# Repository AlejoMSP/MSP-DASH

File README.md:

# MSP-DASH

A digital gauge cluster for a turbocharged 2002 Mazda Miata (NB2) running rusEFI. Three round AMOLED screens show
gauges; one ESP32 "hub" reads the car (CAN bus and its own sensors) and sends everything to them over ESP-NOW.
A small OLED on the hub shows warning lamps and quick pages.

Power in the car (fuse, diode, TVS, buck options): docs/POWER.md.

The stock tach and speedo: `aircore/` (ESP32 DevKitC + two DRV8833 at 5 V, aircore build 8; set up on the hub's Stock gauges page). Pinout and calibration: aircore/README.md.

Current builds: **screens 245**, **hub 70**.

## Hardware

| Board | Role | Address |
|---|---|---|
| ESP32 DevKitC (Freenove terminal board) | **Hub**: CAN, sensors, buttons, brightness, OLED, GPS, accelerometer, 433 MHz | 192.168.55.204 |
| Waveshare ESP32-S3-Touch-AMOLED-1.43 (466x466) | **Left** screen | 192.168.55.201 |
| same | **Center** screen (also logs to its SD card) | 192.168.55.202 |
| same | **Right** screen | 192.168.55.203 |

Hub peripherals: SN65HVD230 CAN transceiver, MAX6675 (EGT), DHT22 (cabin temp/humidity), fuel level sender, GT-U7 GPS,
CC1101 433 MHz receiver (TPMS, in progress), 0.96" SSD1306 OLED, MPU6050 accelerometer, optional MCP23017 input
expanders, optional ADS1115 analog expanders, two page buttons, dash dimmer and lights-on inputs. Every GPIO with its terminal:
[docs/HUB_PINS.md](docs/HUB_PINS.md) (kept in step with `esp32-input/hub_pins.h` by a test).

## What it does

**Screens** (`esp32s3-amoled-bsp-base/`, LVGL 8 on Waveshare's BSP)
- Up to 8 named pages, each a 1-cell, 2-up, 3-up or 2x2 layout of needle, number, half-moon or trend-graph gauges, or
  a page of indicator lamps.
- Per gauge: signal, range, ticks, warning (flash or full-screen alert), peak hold, caption and value placement by
  coordinates, needle thickness and glow, 79 car icons (Material Design Icons) beside or instead of the caption.
- 10 contrast-checked colour schemes, switchable live from a button.
- Web editor with a live screen preview of each cell (caption, icon, sample value, colours), web dashboard,
  OTA updates.
- SD logging on the center screen: start conditions (key on, RPM, speed, any sensor), log files named by the GPS
  date and time, a time column, button log markers.
- Clock gauge from the GPS time (12/24 hour).

**Hub** (`esp32-input/`)
- rusEFI over CAN (DBC-matched), ECU detection, 16 configurable custom CAN sensors (`/custom`).
- Own sensors: EGT, cabin temp/humidity, fuel level, GPS speed/time, accelerometer (lateral, accel/brake and vertical
  G, yaw rate), lamp inputs.
- Brightness from the car's lights and dimmer (or a knob), with day/night levels.
- Inputs and pins page: every GPIO and expander pin with what uses it; move any function to another GPIO; up to 16 inputs on free pins as buttons (active LOW or HIGH, press and hold actions), switches or analog sensors (pressure, voltage, temperature presets, or custom) feeding custom sensor slots; up to 16 outputs (relays, LEDs) switched by a signal, an input or a button.
- Two buttons, configurable on `/buttons`: press or hold 1/2/3/5/10 s, left/right/both. Actions: next/previous page,
  choose screen, go to page, dim/brighten, colour scheme, race mode, clear warning, log marker, show IPs, OLED next page.
- OLED warning panel (`/oled`): 8 lamps with icons, WARNING and DANGER levels, signal or wire-input triggers, plus
  pages (big number, values, G-meter, clock); a lit lamp takes the screen over.
- Bench simulator (`/simulator`) that drives every screen without the car.
- One web app at the hub's address, with a side menu: Dashboard (status tiles, warning panel, key readings), Setup (brightness, clock, accelerometer, I2C devices), Screens (each screen's own pages, picked Left / Center / Right), OLED, Live and custom sensors, Buttons, Logging, Firmware, Simulator, Raw CAN, 433 MHz.

## Getting started

New PC setup (arduino-cli, ESP32 core 3.3.11, libraries, `lv_conf.h`): [PREREQUISITES.md](PREREQUISITES.md).
Copy `esp32-input/wifi_config.h.example` to `wifi_config.h` (and the same for the screens) with your WiFi details.

### Flashing (PowerShell)

Hub (it builds with a few shared headers from the screen folder, copied in first):

```powershell
cls
cd C:\Users\alejo\OneDrive\GIT\MSP-DASH
git pull origin main
copy C:\Users\alejo\OneDrive\GIT\MSP-DASH\esp32s3-amoled-bsp-base\can_parsing.h,C:\Users\alejo\OneDrive\GIT\MSP-DASH\esp32s3-amoled-bsp-base\can_flags.h,C:\Users\alejo\OneDrive\GIT\MSP-DASH\esp32s3-amoled-bsp-base\gauge_config.h,C:\Users\alejo\OneDrive\GIT\MSP-DASH\esp32s3-amoled-bsp-base\link_packets.h,C:\Users\alejo\OneDrive\GIT\MSP-DASH\esp32s3-amoled-bsp-base\simulator.h,C:\Users\alejo\OneDrive\GIT\MSP-DASH\esp32s3-amoled-bsp-base\simulator.cpp,C:\Users\alejo\OneDrive\GIT\MSP-DASH\esp32s3-amoled-bsp-base\custom_slots.h,C:\Users\alejo\OneDrive\GIT\MSP-DASH\esp32s3-amoled-bsp-base\color_presets.h,C:\Users\alejo\OneDrive\GIT\MSP-DASH\esp32s3-amoled-bsp-base\button_actions.h,C:\Users\alejo\OneDrive\GIT\MSP-DASH\esp32s3-amoled-bsp-base\gps_time.h C:\Users\alejo\OneDrive\GIT\MSP-DASH\esp32-input\
arduino-cli compile --clean --fqbn esp32:esp32:esp32:FlashFreq=40,FlashMode=dio,PartitionScheme=min_spiffs --build-path C:\esp32build-input C:\Users\alejo\OneDrive\GIT\MSP-DASH\esp32-input
curl.exe -s -H "Expect:" -w " HTTP %{http_code}" -F "firmware=@C:\esp32build-input\esp32-input.ino.bin" http://192.168.55.204/update
```

Screens (all three):

```powershell
cls
cd C:\Users\alejo\OneDrive\GIT\MSP-DASH
arduino-cli compile --clean --fqbn esp32:esp32:esp32s3:PSRAM=opi,FlashSize=16M,CDCOnBoot=cdc,PartitionScheme=app3M_fat9M_16MB --build-path C:\esp32build C:\Users\alejo\OneDrive\GIT\MSP-DASH\esp32s3-amoled-bsp-base
foreach ($ip in "192.168.55.201","192.168.55.202","192.168.55.203") { $r = curl.exe -s -H "Expect:" -w " HTTP %{http_code}" -F "firmware=@C:\esp32build\esp32s3-amoled-bsp-base.ino.bin" http://$ip/update; Write-Host "$ip -> $r" }
```

Or build with the commands above and upload from the hub's Firmware page: the hub, and all screens from one file.
If a board stops answering over WiFi, flash it over USB with `arduino-cli upload -p COMx --fqbn <same fqbn> --input-dir <build path> <sketch folder>`.

## Tests

Host tests run on a PC, no boards needed: [tests/host/README.md](tests/host/README.md). They cover the gauge config,
logging, simulator, button logic, GPS time, OLED panel and pages, accelerometer math, the CAN decoder, every web page's
script (in Node), a compile check of the whole hub sketch (`hub_typecheck.sh`) and of the screen sources
(`typecheck.sh`).

## Repository

| Path | What |
|---|---|
| `esp32s3-amoled-bsp-base/` | Screen firmware, plus the headers shared with the hub |
| `esp32-input/` | Hub firmware |
| `tests/host/` | Host tests and stubs |
| `tools/icons/` | Icon pipeline: Material Design Icons to LVGL fonts and 1-bit OLED bitmaps, previews |
| `tools/gen_fonts.sh` | Number fonts |
| `docs/` | Design notes, see below |

## Docs

| File | About |
|---|---|
| [CODE_GUIDE.md](docs/CODE_GUIDE.md) | How the code is organised, file by file |
| [HUB_PINS.md](docs/HUB_PINS.md) | Hub wiring, every GPIO with its terminal |
| [CAN-map.md](docs/CAN-map.md), [rusefi.dbc](docs/rusefi.dbc) | rusEFI CAN frames and decoding |
| [RUSEFI_LUA.md](docs/RUSEFI_LUA.md) | Lua script for EGT to rusEFI |
| [HUB_SPEED_SENSORS.md](docs/HUB_SPEED_SENSORS.md) | Hall speed sensor and GPS |
| [CONFIGURABLE_SENSORS.md](docs/CONFIGURABLE_SENSORS.md) | Custom CAN sensor slots |
| [HUB_433MHZ.md](docs/HUB_433MHZ.md) | CC1101 receiver and the TPMS decode work |
| [TODO.md](docs/TODO.md) | Tasks to be done, and the voltage divider values for 3.3 V inputs |
| [TIMELINE.md](docs/TIMELINE.md) | Build-by-build history |
| [esp32s3-amoled-board.md](docs/esp32s3-amoled-board.md) | Screen bring-up history and hardware findings |

## Status and next steps

Working on the bench: screens, hub, CAN from rusEFI, brightness, buttons, simulator, logging, OLED panel and pages, GPS,
accelerometer, the web app. Everything still open is in [docs/TODO.md](docs/TODO.md).

The old WROOM + Nextion firmware was removed in build 149 and early bring-up sketches in build 114; both are in git history.

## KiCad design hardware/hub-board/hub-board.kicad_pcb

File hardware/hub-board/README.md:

# Hub carrier board, rev B

The hub's ESP32 DevKitC plugs into two 19-pin sockets. On the board: the protected 12 V input, the 5 V buck module
header, CAN (SN65HVD230 module), EGT (MAX6675 module: only the thermocouple is wired outside, to its own terminal),
GPS (module on a socket, SMA bulkhead hole at the top edge for an outside antenna), an MCP23017 (16 digital inputs)
and an ADS1115 module (4 analog inputs). Everything else lives off the board and is wired to terminals: CC1101, OLED,
MPU6050, DHT22, fuel sender, knob, lights, dimmer, buttons. 148 x 112 mm, 2 layers, through-hole only.

Rev A (all modules on sockets, 5.08 mm screw terminals) is in git history.

Files: `hub-board.kicad_pro` (open in KiCad 7 or 8), `hub-board.kicad_sch`, `hub-board.kicad_pcb`,
`hub-board-gerbers.zip` (JLCPCB: 2 layers, 1.6 mm, 1 oz), `gerbers/`, `drc.rpt`.

## Connectors

| Ref | Connector | Pins |
|---|---|---|
| J3 | 12 V in: Molex Mini-Fit Jr 5569-02A2 (right angle, PCB pegs). Plug: housing 5557-02R, pins 5556 | 1 +12V, 2 GND |
| J5 | 5 V out (screens, gauge board): Mini-Fit Jr 5569-02A2 | 1 +5V, 2 GND |
| J20 | MCP23017 port A: 8 inputs | A0-A7 |
| J21 | MCP23017 port B: 8 inputs | B0-B7 |
| J22 | ESP32 inputs | FUEL (IO36), KNOB (IO34), LIGHTS (IO35), DIMMER (IO32), NEXT (IO25), PREV (IO26), IO2, GND |
| J23 | ADS1115 | A0, A1, A2, A3, 3V3, GND |
| J24 | Sensor power | 3V3, GND, 3V3, GND |
| J25 | CAN | CANH, CANL, GND |
| J26 | CC1101 (outside) | 3V3, GND, SCK (IO14), MOSI (IO13), MISO (IO39), CSN (IO27), GDO0 (IO33) |
| J27 | I2C (OLED, MPU6050) + DHT22 | 3V3, GND, SDA (IO5), SCL (IO15), DHT (IO4), GND |

Signal terminals: Phoenix MC 1,5/x-G-3.5 headers (3.5 mm, pluggable). Plugs: Phoenix MC 1,5/x-ST-3,5 (same pin count).
Not on any terminal: IO0 and IO12 (boot pins: a signal on them at power-up stops the ESP32 starting), IO16/IO17 (GPS on
the board), IO18/IO19/IO23 (MAX6675), IO21/IO22 (CAN).

## Inputs

- **MCP23017 (U1, address 0x27):** each input through 10k. Takes 12 V signals (the chip's clamp limits the current
  to under 1 mA) and switches to ground (use the internal pull-up on the Inputs page).
- **ESP32 inputs:** FUEL 1k + 3.3 V clamp (pull-up position not fitted); KNOB 1k + clamp (0-3.3 V pot: use J24 for
  3V3/GND); LIGHTS and DIMMER 47k/10k dividers + clamp + 100 nF (12 V signals); NEXT and PREV 1k (buttons to
  ground, internal pull-up); IO2 10k + clamp.
- **ADS1115:** each channel has a series resistor (1k fitted), a divider resistor to ground and a pull-up to 3.3 V
  (not fitted). 0-3.3 V sensor: as built. 0-5 V sensor: fit the divider (for example 1k series stays, 2k to ground).
  Resistive sender (fuel, temperature): fit the pull-up (for example 1k). Values per channel:

| Channel | Series | To ground | Pull-up |
|---|---|---|---|
| A0 | R26 (1k) | R27 (not fitted) | R28 (not fitted) |
| A1 | R29 (1k) | R30 (not fitted) | R31 (not fitted) |
| A2 | R32 (1k) | R33 (not fitted) | R34 (not fitted) |
| A3 | R35 (1k) | R36 (not fitted) | R37 (not fitted) |
- **Outside modules:** 100 ohm in series only (fast buses). 4k7 I2C pull-ups and a 10k DHT pull-up on the board.

## Check before ordering

1. **DevKitC row spacing:** 25.4 mm between the 19-pin rows. Measure yours.
2. **Module pin order** (square pad = pin 1): SN65HVD230 J7 3V3, GND, CTX, CRX + J8 CANH, CANL; MAX6675 J9 GND,
   VCC, SCK, CS, SO; ADS1115 J12 VDD, GND, SCL, SDA, ADDR, ALRT, A0-A3; GPS J15 VCC (5 V), RX, TX, GND; buck J4
   IN+, IN-, OUT+, OUT-.
3. **GPS antenna:** a u.FL-to-SMA bulkhead pigtail (about 10 cm) from the module to the 6.4 mm hole (H5).
4. **CAN termination:** fit JP1 only if the bus needs another 120 ohm.

## Regenerating

`tools/gen_hub_board.py` holds the parts list, placement and nets. With KiCad 7's Python:

```
python3 tools/gen_hub_board.py place                     # board with parts, and hub-board.dsn for the router
java -jar freerouting-2.0.1.jar --gui.enabled=false -de hub-board.dsn -do run.ses -mp 25 -mt 1
python3 tools/gen_hub_board.py finish hardware/hub-board/run.ses   # routes in, ground pours, DRC
```

Freerouting 2.0.1 single-threaded (`-mt 1`): multi-threaded and 2.1.0 runs left connections out of the .ses. If DRC
still lists unconnected pads, export a DSN from that board and route it once more (the second pass keeps the first
pass's tracks and adds the rest); that is how this board's `hub-board.ses` was made.

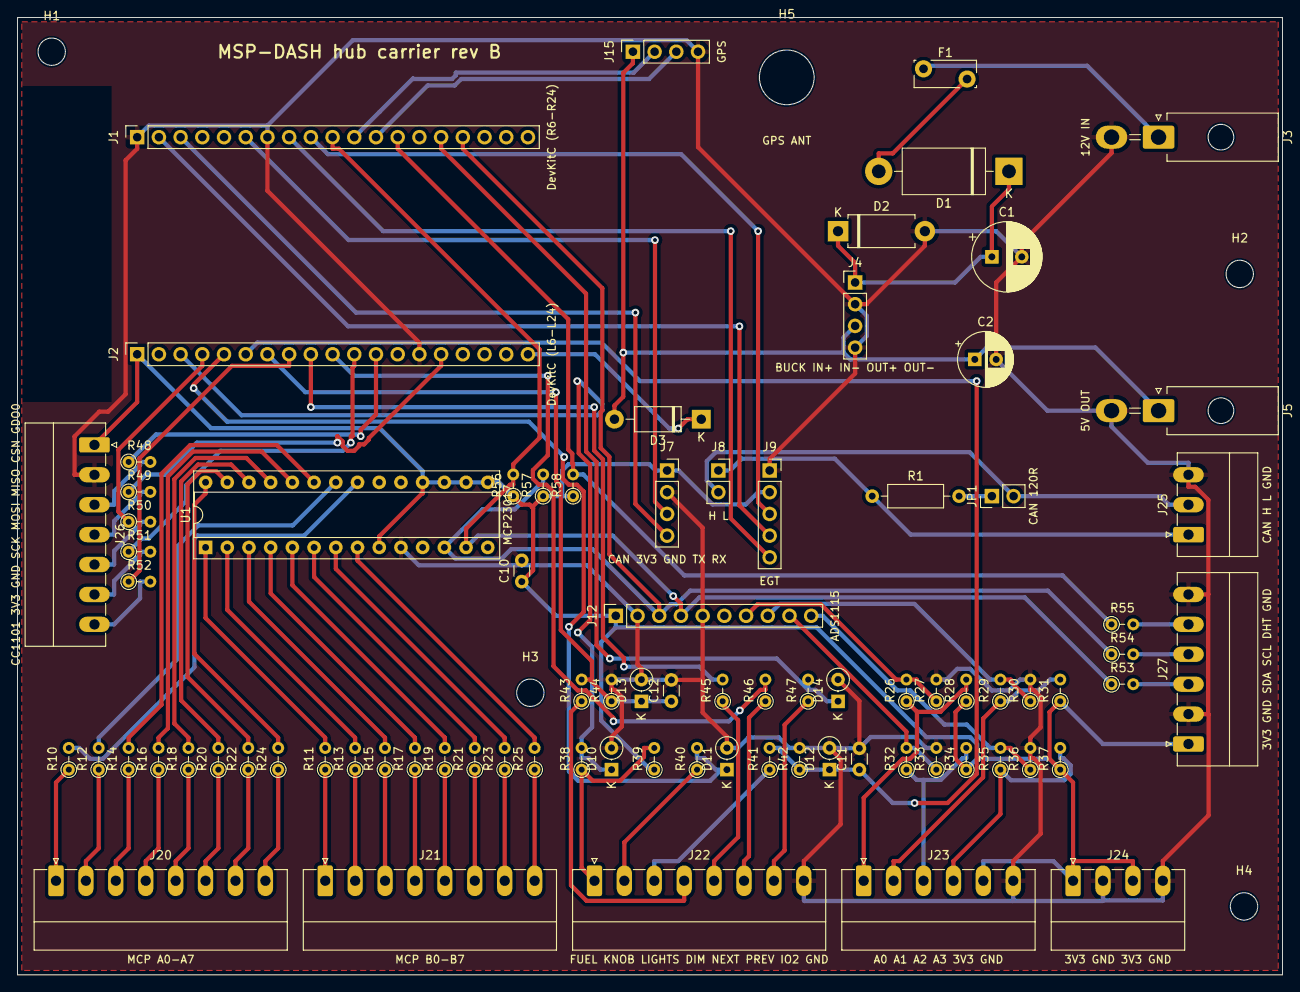
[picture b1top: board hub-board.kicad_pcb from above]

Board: 2 copper layers, 148.0 x 112.0 mm, 89 parts (0 on the bottom side), 87 nets.

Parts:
C1: 470uF 35V; CP_Radial_D8.0mm_P3.50mm
C2: 100uF 10V; CP_Radial_D6.3mm_P2.50mm
C10, C11, C12: 100nF; C_Disc_D3.0mm_W1.6mm_P2.50mm
D1: 1N5822; D_DO-201AD_P15.24mm_Horizontal
D2: P6KE18A TVS; D_DO-15_P10.16mm_Horizontal
D3: 1N5819; D_DO-41_SOD81_P10.16mm_Horizontal
D10, D11, D12, D13, D14: BZX79-C3V3; D_DO-35_SOD27_P2.54mm_Vertical_KathodeUp
F1: MF-RG300 PTC; Fuse_Bourns_MF-RG300
H1, H2, H3, H4: M3; MountingHole_3.2mm_M3
H5: GPS ANT; MountingHole_6.4mm_M6
J1: DevKitC (R6-R24); PinSocket_1x19_P2.54mm_Vertical
J2: DevKitC (L6-L24); PinSocket_1x19_P2.54mm_Vertical
J3: 12V IN; Molex_Mini-Fit_Jr_5569-02A2_2x01_P4.20mm_Horizontal
J4: BUCK IN+ IN- OUT+ OUT-; PinHeader_1x04_P2.54mm_Vertical
J5: 5V OUT; Molex_Mini-Fit_Jr_5569-02A2_2x01_P4.20mm_Horizontal
J7: CAN 3V3 GND TX RX; PinSocket_1x04_P2.54mm_Vertical
J8: H L; PinSocket_1x02_P2.54mm_Vertical
J9: EGT; PinSocket_1x05_P2.54mm_Vertical
J12: ADS1115; PinSocket_1x10_P2.54mm_Vertical
J15: GPS; PinSocket_1x04_P2.54mm_Vertical
J20: MCP A0-A7; PhoenixContact_MC_1,5_8-G-3.5_1x08_P3.50mm_Horizontal
J21: MCP B0-B7; PhoenixContact_MC_1,5_8-G-3.5_1x08_P3.50mm_Horizontal
J22: FUEL KNOB LIGHTS DIM NEXT PREV IO2 GND; PhoenixContact_MC_1,5_8-G-3.5_1x08_P3.50mm_Horizontal
J23: A0 A1 A2 A3 3V3 GND; PhoenixContact_MC_1,5_6-G-3.5_1x06_P3.50mm_Horizontal
J24: 3V3 GND 3V3 GND; PhoenixContact_MC_1,5_4-G-3.5_1x04_P3.50mm_Horizontal
J25: CAN H L GND; PhoenixContact_MC_1,5_3-G-3.5_1x03_P3.50mm_Horizontal
J26: CC1101 3V3 GND SCK MOSI MISO CSN GDO0; PhoenixContact_MC_1,5_7-G-3.5_1x07_P3.50mm_Horizontal
J27: 3V3 GND SDA SCL DHT GND; PhoenixContact_MC_1,5_6-G-3.5_1x06_P3.50mm_Horizontal
JP1: CAN 120R; PinHeader_1x02_P2.54mm_Vertical
R1: 120R; R_Axial_DIN0207_L6.3mm_D2.5mm_P10.16mm_Horizontal
R10, R11, R12, R13, R14, R15, R16, R17, R18, R19, R20, R21, R22, R23, R24, R25, R42, R44, R47, R58: 10k; R_Axial_DIN0204_L3.6mm_D1.6mm_P2.54mm_Vertical
R26, R29, R32, R35, R38, R40, R45, R46: 1k; R_Axial_DIN0204_L3.6mm_D1.6mm_P2.54mm_Vertical
R27, R28, R30, R31, R33, R34, R36, R37, R39: DNP; R_Axial_DIN0204_L3.6mm_D1.6mm_P2.54mm_Vertical
R41, R43: 47k; R_Axial_DIN0204_L3.6mm_D1.6mm_P2.54mm_Vertical
R48, R49, R50, R51, R52, R53, R54, R55: 100R; R_Axial_DIN0204_L3.6mm_D1.6mm_P2.54mm_Vertical
R56, R57: 4k7; R_Axial_DIN0204_L3.6mm_D1.6mm_P2.54mm_Vertical
U1: MCP23017; DIP-28_W7.62mm_Socket

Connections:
12V_F: D1.2, F1.2
12V_IN: F1.1, J3.1
+3V3: C10.1, J2.1, J7.1, J9.2, J12.1, J23.5, J24.1, J24.3, J26.1, J27.1, R28.1, R31.1, R34.1, R37.1, R39.1, R56.1, R57.1, R58.1, U1.9, U1.15, U1.16, U1.17, U1.18
+5V: C2.1, D3.2, J4.3, J5.1, J15.1
+5V_ESP: D3.1, J2.19
+12V: C1.1, D1.1, D2.1, J4.1
ADS_A0: J12.7, R26.2, R27.1
ADS_A1: J12.8, R29.2, R30.1
ADS_A2: J12.9, R32.2, R33.1
ADS_A3: J12.10, R35.2, R36.1
ADS_IN0: J23.1, R26.1, R28.2
ADS_IN1: J23.2, R29.1, R31.2
ADS_IN2: J23.3, R32.1, R34.2
ADS_IN3: J23.4, R35.1, R37.2
BTN_NEXT: J2.9, R45.2
BTN_NEXT_IN: J22.5, R45.1
BTN_PREV: J2.10, R46.2
BTN_PREV_IN: J22.6, R46.1
CANH: J8.1, J25.1, R1.1
CANL: J8.2, J25.2, JP1.2
CAN_RX: J1.3, J7.4
CAN_T: JP1.1, R1.2
CAN_TX: J1.6, J7.3
DHT_DATA: J1.13, R55.1, R58.2
DHT_DATA_X: J27.5, R55.2
DIMMER: C12.1, D13.1, J2.7, R43.2, R44.1
DIMMER_IN: J22.4, R43.1
EGT_CS: J1.2, J9.4
EGT_SCK: J1.9, J9.3
EGT_SO: J1.8, J9.5
FUEL: D10.1, J2.3, R38.2
FUEL_IN: J22.1, R38.1, R39.2
GND: C1.2, C2.2, C10.2, C11.2, C12.2, D2.2, D10.2, D11.2, D12.2, D13.2, D14.2, J1.1, J1.7, J2.14, J3.2, J4.2, J4.4, J5.2, J7.2, J9.1, J12.2, J12.5, J15.4, J22.8, J23.6, J24.2, J24.4, J25.3, J26.2, J27.2, J27.6, R27.2, R30.2, R33.2, R36.2, R42.2, R44.2, U1.10
GPS_RXD: J1.11, J15.2
GPS_TXD: J1.12, J15.3
I2C_SCL: J1.16, J12.3, R54.1, R57.2, U1.12
I2C_SCL_X: J27.4, R54.2
I2C_SDA: J1.10, J12.4, R53.1, R56.2, U1.13
I2C_SDA_X: J27.3, R53.2
KNOB: D11.1, J2.5, R40.2
KNOB_IN: J22.2, R40.1
LIGHTS: C11.1, D12.1, J2.6, R41.2, R42.1
LIGHTS_IN: J22.3, R41.1
MCP_A0: R10.2, U1.21
MCP_A0_IN: J20.1, R10.1
MCP_A1: R12.2, U1.22
MCP_A1_IN: J20.2, R12.1
MCP_A2: R14.2, U1.23
MCP_A2_IN: J20.3, R14.1
MCP_A3: R16.2, U1.24
MCP_A3_IN: J20.4, R16.1
MCP_A4: R18.2, U1.25
MCP_A4_IN: J20.5, R18.1
MCP_A5: R20.2, U1.26
MCP_A5_IN: J20.6, R20.1
MCP_A6: R22.2, U1.27
MCP_A6_IN: J20.7, R22.1
MCP_A7: R24.2, U1.28
MCP_A7_IN: J20.8, R24.1
MCP_B0: R11.2, U1.1
MCP_B0_IN: J21.1, R11.1
MCP_B1: R13.2, U1.2
MCP_B1_IN: J21.2, R13.1
MCP_B2: R15.2, U1.3
MCP_B2_IN: J21.3, R15.1
MCP_B3: R17.2, U1.4
MCP_B3_IN: J21.4, R17.1
MCP_B4: R19.2, U1.5
MCP_B4_IN: J21.5, R19.1
MCP_B5: R21.2, U1.6
MCP_B5_IN: J21.6, R21.1
MCP_B6: R23.2, U1.7
MCP_B6_IN: J21.7, R23.1
MCP_B7: R25.2, U1.8
MCP_B7_IN: J21.8, R25.1
RF_CSN: J2.11, R51.1
RF_CSN_X: J26.6, R51.2
RF_GDO0: J2.8, R52.1
RF_GDO0_X: J26.7, R52.2
RF_MISO: J2.4, R50.1
RF_MISO_X: J26.5, R50.2
RF_MOSI: J2.15, R49.1
RF_MOSI_X: J26.4, R49.2
RF_SCK: J2.12, R48.1
RF_SCK_X: J26.3, R48.2
SPARE_IO2: D14.1, J1.15, R47.2
SPARE_IO2_IN: J22.7, R47.1

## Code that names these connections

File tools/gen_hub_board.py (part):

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part("J5", "5V OUT Mini-Fit Jr", MINIFIT, seq([("+5V", "+5V"), ("GND", "GND")]), 133.5, 46, 270); label("J5", "5V OUT")

# GPS on board; SMA bulkhead hole at the top edge for the outside antenna (u.FL-to-SMA pigtail from the module)
part("J15", "GPS (VCC RX TX GND)", SOCK % 4, seq([("VCC", "+5V"), ("RX", "GPS_RXD"), ("TX", "GPS_TXD"), ("GND", "GND")]), 72, 4, 90); label("J15", "GPS")
part("H5", "SMA bulkhead (GPS antenna)", "MountingHole:MountingHole_6.4mm_M6", {}, 90, 7, 0); label("H5", "GPS ANT")

# CAN transceiver module + termination
part("J7", "SN65HVD230 (3V3 GND CTX CRX)", SOCK % 4, seq([("3V3", "+3V3"), ("GND", "GND"), ("CTX", "CAN_TX"), ("CRX", "CAN_RX")]), 76, 53, 0); label("J7", "CAN 3V3 GND TX RX")
part("J8", "SN65HVD230 (CANH CANL)", SOCK % 2, seq([("CANH", "CANH"), ("CANL", "CANL")]), 82, 53, 0); label("J8", "H L")
part("R1", "120R", RES, {"1": ("1", "CANH"), "2": ("2", "CAN_T")}, 100, 56, 0)
part("JP1", "CAN 120R", "Connector_PinHeader_2.54mm:PinHeader_1x02_P2.54mm_Vertical", {"1": ("1", "CAN_T"), "2": ("2", "CANL")}, 114, 56, 90); label("JP1", "CAN 120R")

# MAX6675 module: its own screw terminal takes the thermocouple
part("J9", "MAX6675 (GND VCC SCK CS SO)", SOCK % 5, seq([("GND", "GND"), ("VCC", "+3V3"), ("SCK", "EGT_SCK"), ("CS", "EGT_CS"), ("SO", "EGT_SO")]), 88, 53, 0); label("J9", "EGT")

# MCP23017 (DIP-28, address 0x27: A0-A2 high), 16 inputs through 10k
mcp = {"9": ("VDD", "+3V3"), "10": ("VSS", "GND"), "11": ("NC", None), "12": ("SCL", "I2C_SCL"), "13": ("SDA", "I2C_SDA"), "14": ("NC", None),
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
# ADS1115 module: each channel series (fitted 1k), divider to GND and pull-up to 3.3 V (fit as needed)
part("J12", "ADS1115", SOCK % 10, seq([("VDD", "+3V3"), ("GND", "GND"), ("SCL", "I2C_SCL"), ("SDA", "I2C_SDA"), ("ADDR", "GND"), ("ALRT", None),
     ("A0", "ADS_A0"), ("A1", "ADS_A1"), ("A2", "ADS_A2"), ("A3", "ADS_A3")]), 70, 70, 90); label("J12", "ADS1115")
for i in range(4):
    x, y = 104 + 11 * (i % 2), (80, 88)[i // 2]
    R("1k", f"ADS_IN{i}", f"ADS_A{i}", x, y)
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    if clamp: Z(net, x0, y0); x0 += 3.5
    if cap: Cc(net, x0, y0); x0 += 4.5
    x0 += 1.5
inp("FUEL", "1k"); R("DNP", "+3V3", "FUEL_IN", x0, y0); x0 += 5
inp("KNOB", "1k")
inp("LIGHTS", "47k", "10k", cap=True)
x0, y0 = 66, 80   # second row
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part("J20", "MCP GPA0-7", MC % (8, 8), seq([(f"A{i}", f"MCP_A{i}_IN") for i in range(8)]), 4.5, 101, 0); label("J20", "MCP A0-A7")
part("J21", "MCP GPB0-7", MC % (8, 8), seq([(f"B{i}", f"MCP_B{i}_IN") for i in range(8)]), 36, 101, 0); label("J21", "MCP B0-B7")
part("J22", "INPUTS", MC % (8, 8), seq([("FUEL", "FUEL_IN"), ("KNOB", "KNOB_IN"), ("LIGHTS", "LIGHTS_IN"), ("DIMMER", "DIMMER_IN"), ("NEXT", "BTN_NEXT_IN"),
     ("PREV", "BTN_PREV_IN"), ("IO2", "SPARE_IO2_IN"), ("GND", "GND")]), 67.5, 101, 0); label("J22", "FUEL KNOB LIGHTS DIM NEXT PREV IO2 GND")
part("J23", "ADS A0-A3, 3V3, GND", MC % (6, 6), seq([("A0", "ADS_IN0"), ("A1", "ADS_IN1"), ("A2", "ADS_IN2"), ("A3", "ADS_IN3"), ("3V3", "+3V3"), ("GND", "GND")]), 99, 101, 0); label("J23", "A0 A1 A2 A3 3V3 GND")
part("J24", "3V3 GND (sensors)", MC % (4, 4), seq([("3V3", "+3V3"), ("GND", "GND"), ("3V3", "+3V3"), ("GND", "GND")]), 123.5, 101, 0); label("J24", "3V3 GND 3V3 GND")
part("J25", "CAN (H L GND)", MC % (3, 3), seq([("CANH", "CANH"), ("CANL", "CANL"), ("GND", "GND")]), 137, 60.5, 90); label("J25", "CAN H L GND")
part("J26", "SPI (CC1101)", MC % (7, 7), seq([("3V3", "+3V3"), ("GND", "GND"), ("SCK", "RF_SCK_X"), ("MOSI", "RF_MOSI_X"), ("MISO", "RF_MISO_X"), ("CSN", "RF_CSN_X"), ("GDO0", "RF_GDO0_X")]), 9, 50, 270); label("J26", "CC1101 3V3 GND SCK MOSI MISO CSN GDO0")
part("J27", "I2C (OLED, MPU6050) + DHT22", MC % (6, 6), seq([("3V3", "+3V3"), ("GND", "GND"), ("SDA", "I2C_SDA_X"), ("SCL", "I2C_SCL_X"), ("DHT", "DHT_DATA_X"), ("GND", "GND")]), 137, 85, 90); label("J27", "3V3 GND SDA SCL DHT GND")

for i, (x, y) in enumerate(((4, 4), (143, 30), (60, 79), (143.5, 104))):
    part(f"H{i + 1}", "M3", "MountingHole:MountingHole_3.2mm_M3", {}, x, y, 0)
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
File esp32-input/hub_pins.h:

// hub_pins.h - EVERY GPIO the hub uses, in one place. Each function ("role") has a default GPIO; the Inputs page can
// move a role to another GPIO (saved, applied at the next start). docs/HUB_PINS.md lists the defaults with their
// terminals, and tests/host/test_hub_pins.js fails if the two disagree. Pure C: host-tested.
#pragma once
#include <stdint.h>
#include <stdbool.h>

// ---- what each GPIO of the ESP32-WROOM can do ----
enum { CAP_IN = 1, CAP_OUT = 2, CAP_ADC = 4, CAP_PULLUP = 8 };   // ADC = ADC1 (ADC2 stops working with WiFi on)
static inline uint8_t gpio_caps(int g) {
  switch (g) {
    case 32: case 33: return CAP_IN | CAP_OUT | CAP_ADC | CAP_PULLUP;
    case 34: case 35: case 36: case 39: return CAP_IN | CAP_ADC;           // input only, no internal pull-up
    case 0: case 2: case 4: case 5: case 12: case 13: case 14: case 15: case 16: case 17: case 18: case 19:
    case 21: case 22: case 23: case 25: case 26: case 27: return CAP_IN | CAP_OUT | CAP_PULLUP;
    default: return 0;   // 1, 3 (USB serial), 6-11 (flash), and numbers the chip does not have
  }
}
// A warning for a pin with a power-up rule ("" = none).
static inline const char *gpio_note(int g) {
  switch (g) {
    case 0: return "BOOT button: must not be held LOW at power-up";
    case 2: return "must not be held HIGH while flashing over USB";
    case 12: return "must not be held HIGH at power-up";
    case 15: return "LOW at power-up silences the boot messages";
    case 34: case 35: case 36: case 39: return "input only, no internal pull-up";
    default: return "";
  }
}
#define GPIO_LIST { 0, 2, 4, 5, 12, 13, 14, 15, 16, 17, 18, 19, 21, 22, 23, 25, 26, 27, 32, 33, 34, 35, 36, 39 }

// ---- the hub's fixed functions ----
// Hub 53 took the two page buttons out of this list (they are ordinary buttons on the Buttons page now). A map saved
// before that has 21 entries: PIN_MAP_OLD_COUNT, buttons first (next, previous), then the rest in this order.
#define PIN_MAP_OLD_COUNT 21
enum HubPinRole {
  PR_FUEL, PR_POT, PR_LIGHTS, PR_DIMMER, PR_CAN_TX, PR_CAN_RX, PR_EGT_SCK, PR_EGT_SO, PR_EGT_CS,
  PR_GPS_RX, PR_GPS_TX, PR_DHT, PR_RF_GDO0, PR_RF_CS, PR_RF_SCK, PR_RF_MOSI, PR_RF_MISO, PR_I2C_SDA, PR_I2C_SCL, PR_COUNT
};
typedef struct { const char *key; const char *name; uint8_t def; uint8_t need; const char *term; } HubPinRoleInfo;
// key: short id for the web page and NVS; def: default GPIO; need: CAP_ bits the pin must have; term: default terminal.
static const HubPinRoleInfo HUB_PIN_ROLES[PR_COUNT] = {
  { "fuel",     "Fuel level sender",            36, CAP_ADC,             "L8"  },
  { "pot",      "Brightness knob",              34, CAP_ADC,             "L10" },
  { "lights",   "Lights-on wire (divider)",     35, CAP_ADC,             "L11" },
  { "dimmer",   "Dash dimmer (divider)",        32, CAP_ADC,             "L12" },
  { "can_tx",   "CAN TX (SN65HVD230 CTX)",      21, CAP_OUT,             "R11" },
  { "can_rx",   "CAN RX (SN65HVD230 CRX)",      22, CAP_IN,              "R8"  },
  { "egt_sck",  "EGT MAX6675 SCK",              18, CAP_OUT,             "R14" },
  { "egt_so",   "EGT MAX6675 SO",               19, CAP_IN,              "R13" },
  { "egt_cs",   "EGT MAX6675 CS",               23, CAP_OUT,             "R7"  },
  { "gps_rx",   "GPS: GPS TX to hub RX",        16, CAP_IN,              "R17" },
  { "gps_tx",   "GPS: hub TX to GPS RX",        17, CAP_OUT,             "R16" },
  { "dht",      "DHT22 cabin temp/humidity",     4, CAP_IN | CAP_OUT,    "R18" },
  { "rf_gdo0",  "CC1101 GDO0 (data)",           33, CAP_IN,              "L13" },
  { "rf_cs",    "CC1101 CSN",                   27, CAP_OUT,             "L16" },
  { "rf_sck",   "CC1101 SCK",                   14, CAP_OUT,             "L17" },
  { "rf_mosi",  "CC1101 MOSI",                  13, CAP_OUT,             "L20" },
  { "rf_miso",  "CC1101 MISO",                  39, CAP_IN,              "L9"  },
  { "i2c_sda",  "I2C SDA (OLED, MPU6050, MCP23017)", 5, CAP_IN | CAP_OUT, "R15" },
  { "i2c_scl",  "I2C SCL (OLED, MPU6050, MCP23017)", 15, CAP_IN | CAP_OUT, "R21" },
};
// Pins 100.. are MCP23017 expander pins: board 1 PA0..PB7 = 100..115, board 2 = 116..131 (used by buttons, inputs and
// outputs; none of the fixed functions can run through the expander).
#define PIN_MCP_BASE 100
static inline bool pin_is_mcp(int p) { return p >= PIN_MCP_BASE && p < PIN_MCP_BASE + 32; }
// Pins 140.. are ADS1115 analog channels: board 1 (0x48) A0..A3 = 140..143, 0x49 = 144..147, 0x4A, 0x4B (up to 16).
#define PIN_ADS_BASE 140
static inline bool pin_is_ads(int p) { return p >= PIN_ADS_BASE && p < PIN_ADS_BASE + 16; }
// Roles that may sit on an expander pin: none since hub 53 (the two page buttons moved to the Buttons page).
static inline bool pin_role_mcp_ok(int role) { (void)role; return false; }
// Can this role sit on that GPIO (or expander pin)?
static inline bool pin_role_fits(int role, int g) {
  if (role < 0 || role >= PR_COUNT) return false;
  if (pin_is_mcp(g)) return pin_role_mcp_ok(role);
  if (pin_is_ads(g)) return HUB_PIN_ROLES[role].need == CAP_ADC;   // analog-only roles (fuel, knob, lights, dimmer)
  uint8_t c = gpio_caps(g), need = HUB_PIN_ROLES[role].need;
  return c && (c & need) == need;
}
// A whole map: every role on a GPIO that fits it, and no GPIO used twice.
static inline bool pin_map_valid(const uint8_t map[PR_COUNT]) {
  for (int r = 0; r < PR_COUNT; r++) {
    if (!pin_role_fits(r, map[r])) return false;
    for (int q = 0; q < r; q++) if (map[q] == map[r]) return false;
  }
  return true;
}
static inline void pin_map_defaults(uint8_t map[PR_COUNT]) { for (int r = 0; r < PR_COUNT; r++) map[r] = HUB_PIN_ROLES[r].def; }
// A map saved before hub 53: the two button pins out (for the Buttons page), the rest in the new order.
static inline void pin_map_upgrade(const uint8_t old[PIN_MAP_OLD_COUNT], uint8_t map[PR_COUNT], uint8_t *btnNext, uint8_t *btnPrev) {
  *btnNext = old[0]; *btnPrev = old[1];
  for (int r = 0; r < PR_COUNT; r++) map[r] = old[r + 2];
}
#define PIN_BOOT_BTN 0       // the DevKitC's BOOT button: factory reset (first 15 s after power-up), unless GPIO 0 is given to something
#define PIN_BTN_NEXT_DEF 25   // the default page buttons (Buttons page): right / next on GPIO 25 (L14)
#define PIN_BTN_PREV_DEF 26   //                                          left / previous on GPIO 26 (L15)
// The role on a GPIO, or -1.
static inline int pin_map_role_at(const uint8_t map[PR_COUNT], int g) { for (int r = 0; r < PR_COUNT; r++) if (map[r] == g) return r; return -1; }

// The map in use (filled at the start of setup() from NVS "pins", defaults if none or invalid).
extern uint8_t g_pins[PR_COUNT];
#define FUEL_PIN   (g_pins[PR_FUEL])
#define POT_PIN    (g_pins[PR_POT])
#define LIGHTS_PIN (g_pins[PR_LIGHTS])
#define DIMMER_PIN (g_pins[PR_DIMMER])
#define CAN_TX_PIN ((gpio_num_t)g_pins[PR_CAN_TX])
#define CAN_RX_PIN ((gpio_num_t)g_pins[PR_CAN_RX])
#define EGT_SCK    (g_pins[PR_EGT_SCK])
#define EGT_SO     (g_pins[PR_EGT_SO])
#define EGT_CS     (g_pins[PR_EGT_CS])
#define GPS_RX_PIN (g_pins[PR_GPS_RX])
#define GPS_TX_PIN (g_pins[PR_GPS_TX])
#define DHT_PIN    (g_pins[PR_DHT])
#define RF_GDO0    (g_pins[PR_RF_GDO0])
#define RF_CS      (g_pins[PR_RF_CS])
#define RF_SCK     (g_pins[PR_RF_SCK])
#define RF_MOSI    (g_pins[PR_RF_MOSI])
#define RF_MISO    (g_pins[PR_RF_MISO])
#define I2C_SDA    (g_pins[PR_I2C_SDA])
#define I2C_SCL    (g_pins[PR_I2C_SCL])
